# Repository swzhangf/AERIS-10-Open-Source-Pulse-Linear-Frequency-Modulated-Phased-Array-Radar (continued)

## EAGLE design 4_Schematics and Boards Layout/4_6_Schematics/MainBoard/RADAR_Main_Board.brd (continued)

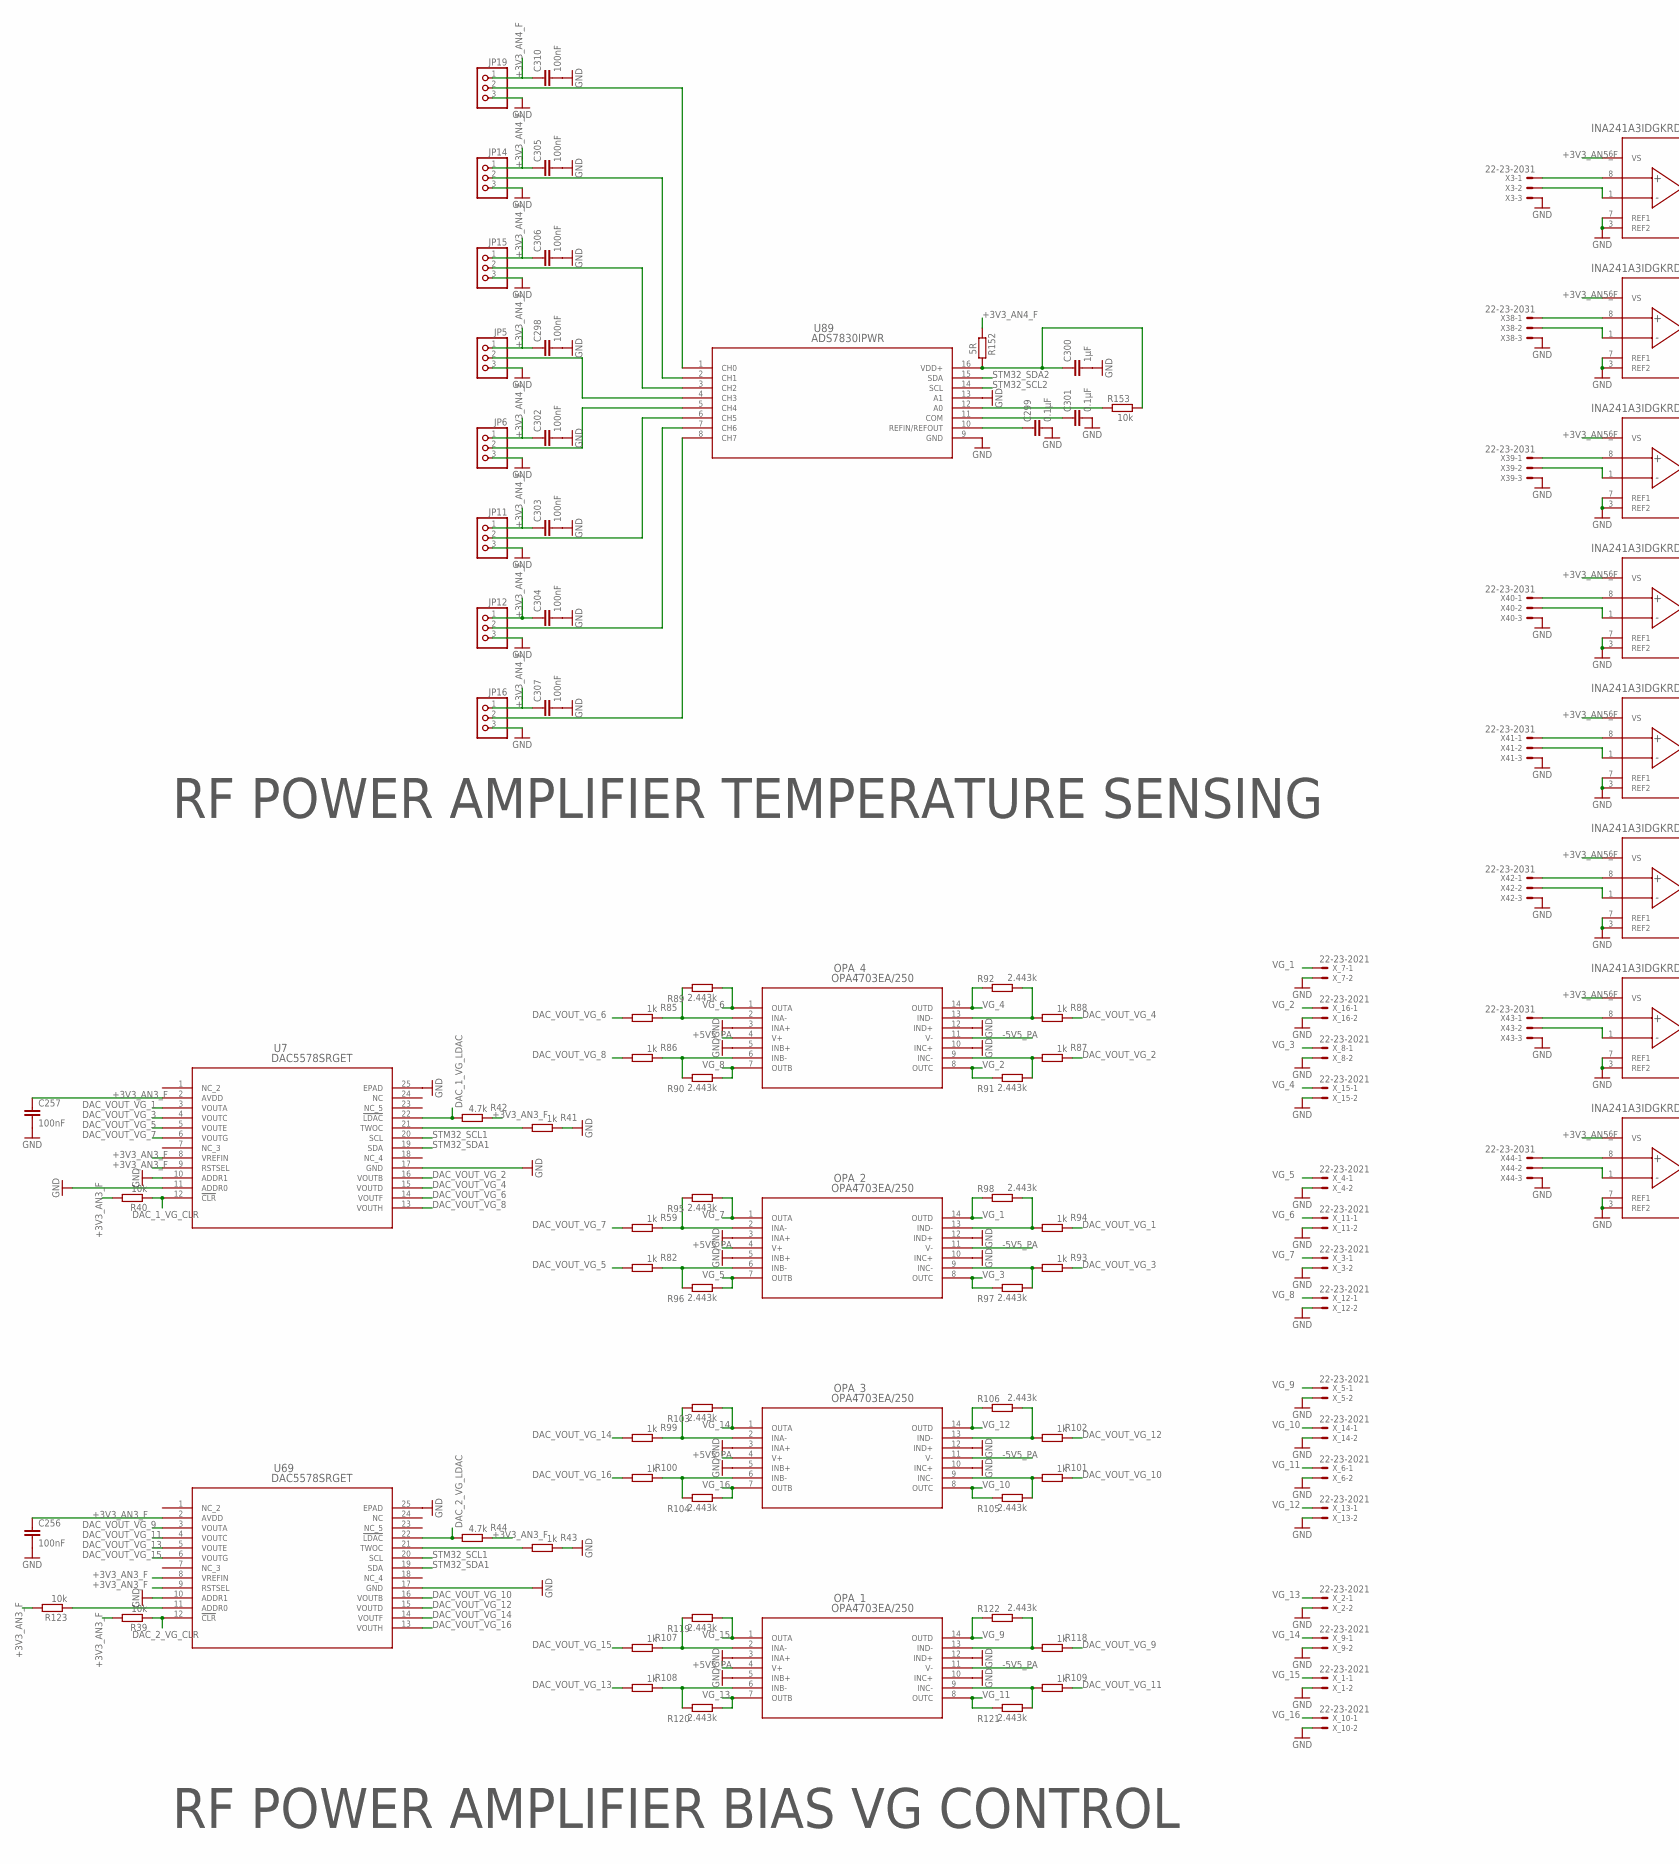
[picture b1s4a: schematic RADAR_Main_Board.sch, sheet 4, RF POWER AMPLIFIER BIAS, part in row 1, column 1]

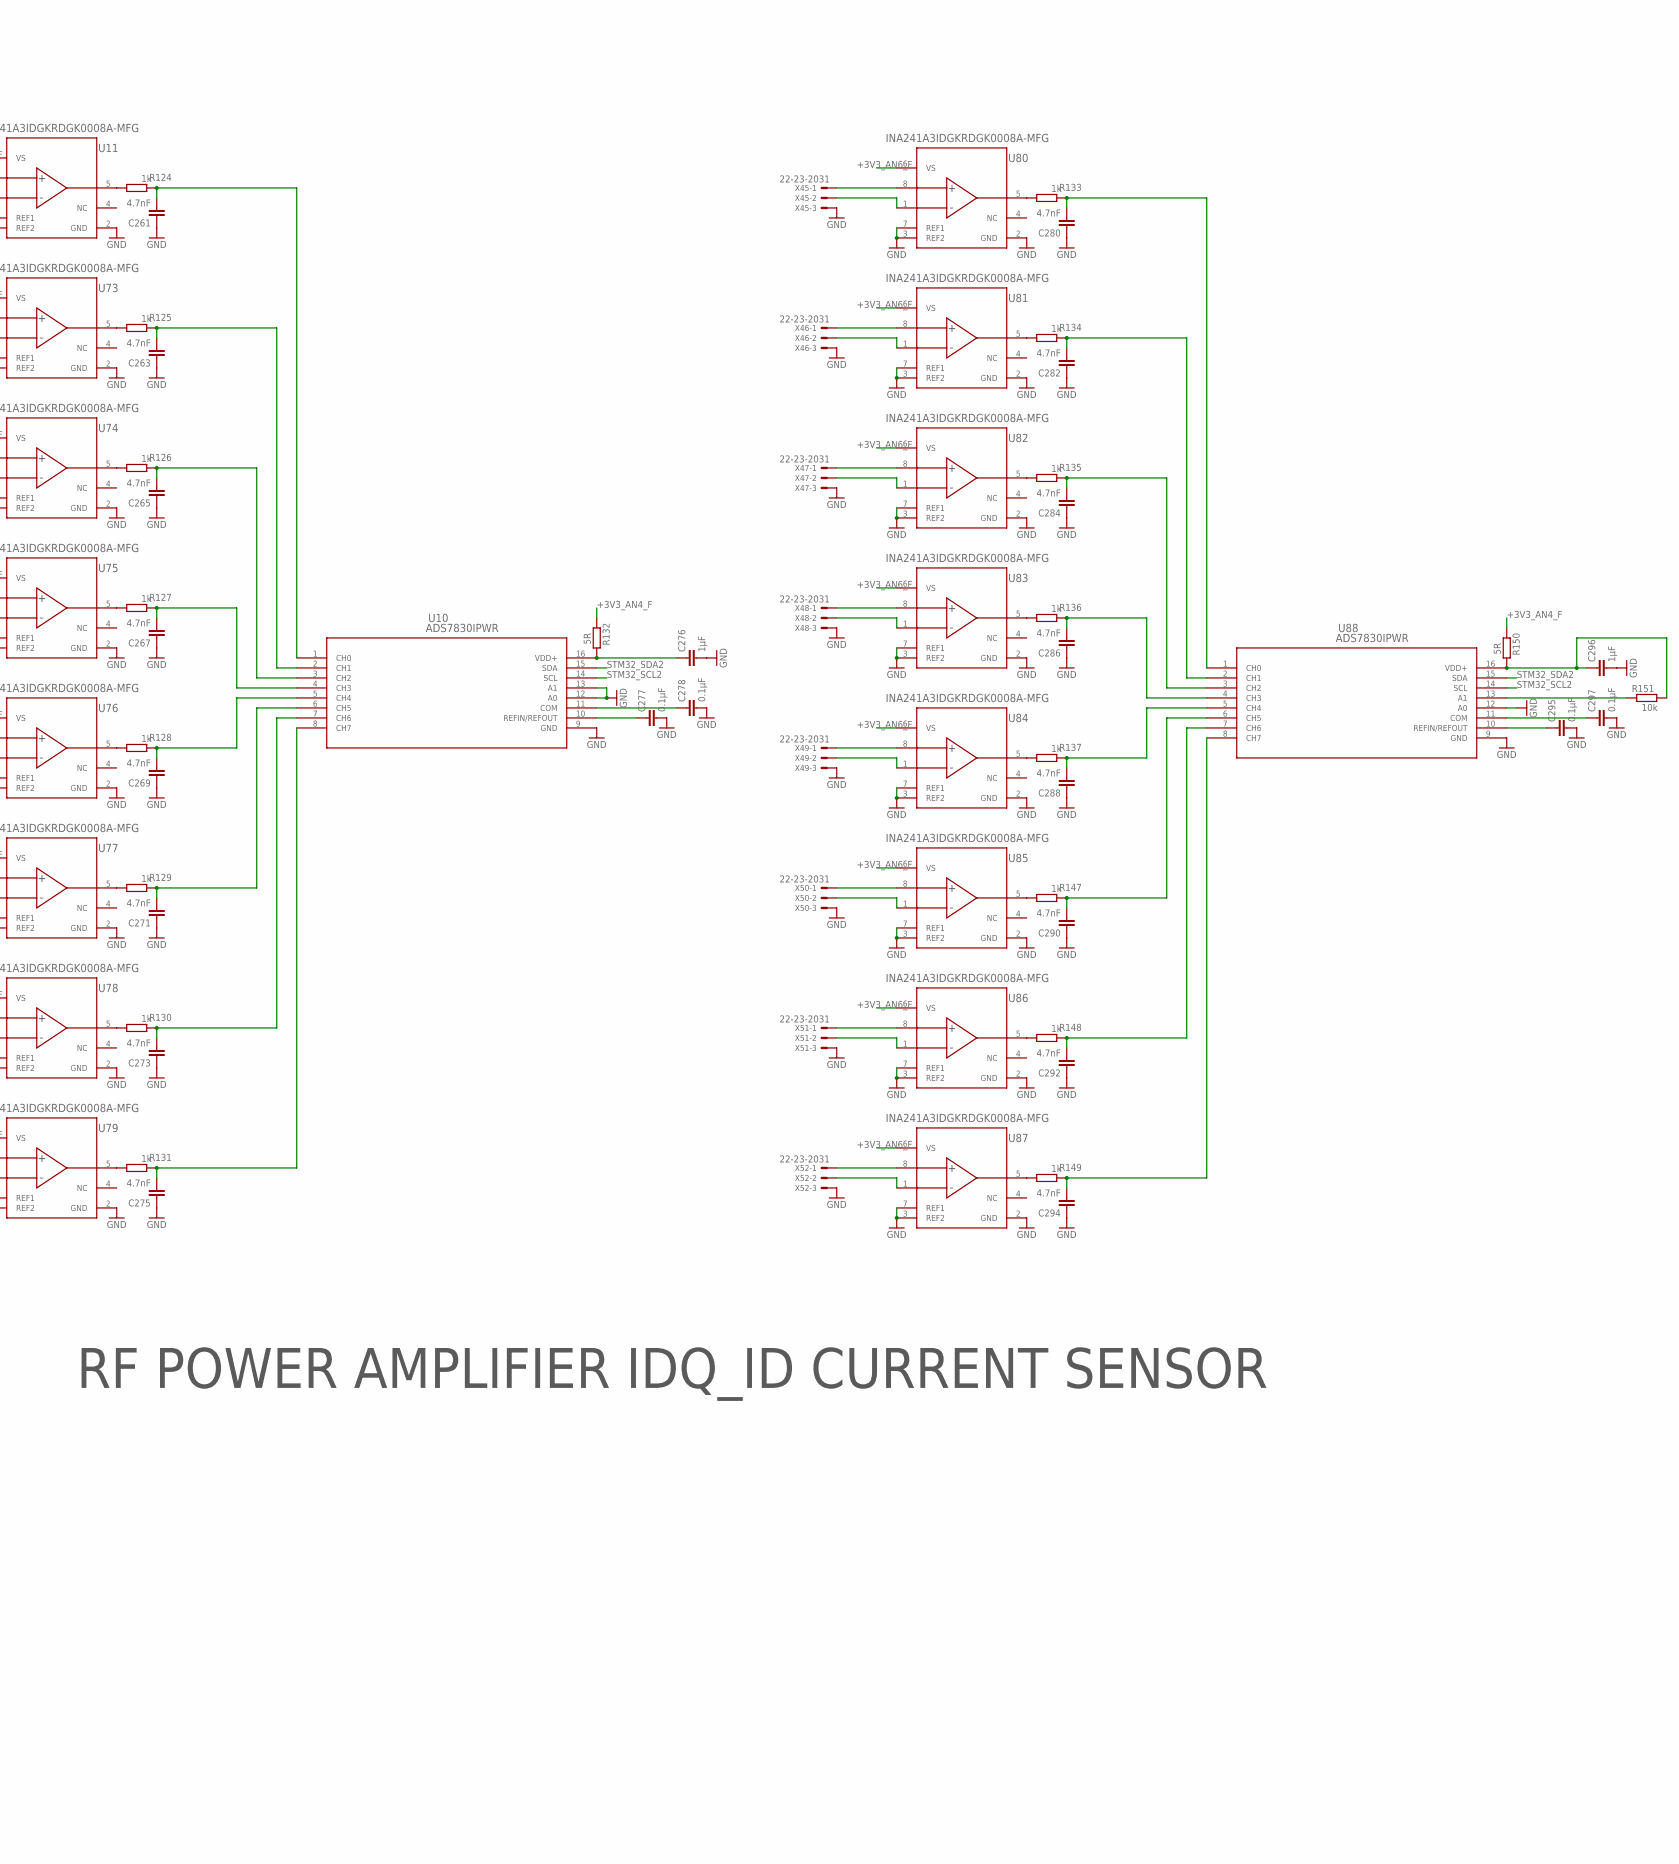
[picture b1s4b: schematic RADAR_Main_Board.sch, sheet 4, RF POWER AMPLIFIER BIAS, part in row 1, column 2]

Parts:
C256, C257, C298, C302, C303, C304, C305, C306, C307, C310: 100nF; C0201
C261, C263, C265, C267, C269, C271, C273, C275, C280, C282, C284, C286, C288, C290, C292, C294: 4.7nF; C0201
C276, C296, C300: 1µF; C0201
C277, C278, C295, C297, C299, C301: 0.1µF; C0201
JP5, JP6, JP11, JP12, JP14, JP15, JP16, JP19: PINHD-1X3; 1X03
OPA_1, OPA_2, OPA_3, OPA_4: OPA4703EA/250; PW14
R39, R40, R123, R151, R153: 10k; R0201
R41, R43, R59, R82, R85, R86, R87, R88, R93, R94, R99, R100, R101, R102, R107, R108, R109, R118, R124, R125, R126, R127, R128, R129, R130, R131, R133, R134, R135, R136, R137, R147, R148, R149: 1k; R0201
R42, R44: 4.7k; R0201
R89, R90, R91, R92, R95, R96, R97, R98, R103, R104, R105, R106, R119, R120, R121, R122: 2.443k; R0201
R132, R150, R152: 5R; R0201
U7, U69: DAC5578SRGET; RGE24_2P7X2P7
U10, U88, U89: ADS7830IPWR; PW16
U11, U73, U74, U75, U76, U77, U78, U79, U80, U81, U82, U83, U84, U85, U86, U87: INA241A3IDGKRDGK0008A-MFG; DGK0008A-MFG
X3, X38, X39, X40, X41, X42, X43, X44, X45, X46, X47, X48, X49, X50, X51, X52: 22-23-2031
X_1, X_2, X_3, X_4, X_5, X_6, X_7, X_8, X_9, X_10, X_11, X_12, X_13, X_14, X_15, X_16: 22-23-2021

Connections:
+3V3_AN3_F: C256.1, C257.1, R39.2, R40.2, R42.1, R44.1, R123.2, U7.2 (AVDD), U7.8 (VREFIN), U7.9 (RSTSEL), U69.2 (AVDD), U69.8 (VREFIN), U69.9 (RSTSEL); also elsewhere on the board
+3V3_AN4_F: C298.1, C302.1, C303.1, C304.1, C305.1, C306.1, C307.1, C310.1, JP5.1, JP6.1, JP11.1, JP12.1, JP14.1, JP15.1, JP16.1, JP19.1, R132.1, R150.1, R152.1; also elsewhere on the board
+3V3_AN5_F: U11.6 (VS), U73.6 (VS), U74.6 (VS), U75.6 (VS), U76.6 (VS), U77.6 (VS), U78.6 (VS), U79.6 (VS); also elsewhere on the board
+3V3_AN6_F: U80.6 (VS), U81.6 (VS), U82.6 (VS), U83.6 (VS), U84.6 (VS), U85.6 (VS), U86.6 (VS), U87.6 (VS); also elsewhere on the board
+5V5_PA: OPA_1.4 (V+), OPA_2.4 (V+), OPA_3.4 (V+), OPA_4.4 (V+); also elsewhere on the board
-5V5_PA: OPA_1.11 (V-), OPA_2.11 (V-), OPA_3.11 (V-), OPA_4.11 (V-); also elsewhere on the board
DAC_1_VG_CLR: R40.1, U7.12 (!CLR); also elsewhere on the board
DAC_1_VG_LDAC: R42.2, U7.22 (!LDAC); also elsewhere on the board
DAC_2_VG_CLR: R39.1, U69.12 (!CLR); also elsewhere on the board
DAC_2_VG_LDAC: R44.2, U69.22 (!LDAC); also elsewhere on the board
DAC_VOUT_VG_1: R94.1, U7.3 (VOUTA)
DAC_VOUT_VG_2: R87.1, U7.16 (VOUTB)
DAC_VOUT_VG_3: R93.1, U7.4 (VOUTC)
DAC_VOUT_VG_4: R88.1, U7.15 (VOUTD)
DAC_VOUT_VG_5: R82.2, U7.5 (VOUTE)
DAC_VOUT_VG_6: R85.2, U7.14 (VOUTF)
DAC_VOUT_VG_7: R59.2, U7.6 (VOUTG)
DAC_VOUT_VG_8: R86.2, U7.13 (VOUTH)
DAC_VOUT_VG_9: R118.1, U69.3 (VOUTA)
DAC_VOUT_VG_10: R101.1, U69.16 (VOUTB)
DAC_VOUT_VG_11: R109.1, U69.4 (VOUTC)
DAC_VOUT_VG_12: R102.1, U69.15 (VOUTD)
DAC_VOUT_VG_13: R108.2, U69.5 (VOUTE)
DAC_VOUT_VG_14: R99.2, U69.14 (VOUTF)
DAC_VOUT_VG_15: R107.2, U69.6 (VOUTG)
DAC_VOUT_VG_16: R100.2, U69.13 (VOUTH)
GND: C256.2, C257.2, C261.1, C263.1, C265.1, C267.1, C269.1, C271.1, C273.1, C275.1, C276.2, C277.2, C278.2, C280.1, C282.1, C284.1, C286.1, C288.1, C290.1, C292.1, C294.1, C295.2, C296.2, C297.2, C298.2, C299.2, C300.2, C301.2, C302.2, C303.2, C304.2, C305.2, C306.2, C307.2, C310.2, JP5.3, JP6.3, JP11.3, JP12.3, JP14.3, JP15.3, JP16.3, JP19.3, OPA_1.3 (INA+), OPA_1.5 (INB+), OPA_1.10 (INC+), OPA_1.12 (IND+), OPA_2.3 (INA+), OPA_2.5 (INB+), OPA_2.10 (INC+), OPA_2.12 (IND+), OPA_3.3 (INA+), OPA_3.5 (INB+), OPA_3.10 (INC+), OPA_3.12 (IND+), OPA_4.3 (INA+), OPA_4.5 (INB+), OPA_4.10 (INC+), OPA_4.12 (IND+), R41.1, R43.1, U7.10 (ADDR1), U7.11 (ADDR0), U7.17 (GND), U7.25 (EPAD), U10.9 (GND), U10.12 (A0), U10.13 (A1), U11.2 (GND), U11.3 (REF2), U11.7 (REF1), U69.10 (ADDR1), U69.17 (GND), U69.25 (EPAD), U73.2 (GND), U73.3 (REF2), U73.7 (REF1), U74.2 (GND), U74.3 (REF2), U74.7 (REF1), U75.2 (GND), U75.3 (REF2), U75.7 (REF1), U76.2 (GND), U76.3 (REF2), U76.7 (REF1), U77.2 (GND), U77.3 (REF2), U77.7 (REF1), U78.2 (GND), U78.3 (REF2), U78.7 (REF1), U79.2 (GND), U79.3 (REF2), U79.7 (REF1), U80.2 (GND), U80.3 (REF2), U80.7 (REF1), U81.2 (GND), U81.3 (REF2), U81.7 (REF1), U82.2 (GND), U82.3 (REF2), U82.7 (REF1), U83.2 (GND), U83.3 (REF2), U83.7 (REF1), U84.2 (GND), U84.3 (REF2), U84.7 (REF1), U85.2 (GND), U85.3 (REF2), U85.7 (REF1), U86.2 (GND), U86.3 (REF2), U86.7 (REF1), U87.2 (GND), U87.3 (REF2), U87.7 (REF1), U88.9 (GND), U88.12 (A0), U89.9 (GND), U89.13 (A1), X3.3, X38.3, X39.3, X40.3, X41.3, X42.3, X43.3, X44.3, X45.3, X46.3, X47.3, X48.3, X49.3, X50.3, X51.3, X52.3, X_1.2, X_2.2, X_3.2, X_4.2, X_5.2, X_6.2, X_7.2, X_8.2, X_9.2, X_10.2, X_11.2, X_12.2, X_13.2, X_14.2, X_15.2, X_16.2; also elsewhere on the board
unnamed: R123.1, U69.11 (ADDR0)
unnamed: R43.2, U69.21 (TWOC)
unnamed: OPA_4.2 (INA-), R85.1, R89.1
unnamed: U11.8 (IN+), X3.1
unnamed: OPA_4.6 (INB-), R86.1, R90.1
unnamed: U11.1 (IN-), X3.2
unnamed: R124.2, U11.5 (OUT)
unnamed: C261.2, R124.1, U10.1 (CH0)
unnamed: U73.8 (IN+), X38.1
unnamed: OPA_4.9 (INC-), R87.2, R91.2
unnamed: U73.1 (IN-), X38.2
unnamed: R125.2, U73.5 (OUT)
unnamed: OPA_4.13 (IND-), R88.2, R92.2
unnamed: C263.2, R125.1, U10.2 (CH1)
unnamed: U74.8 (IN+), X39.1
unnamed: U74.1 (IN-), X39.2
unnamed: R126.2, U74.5 (OUT)
unnamed: R41.2, U7.21 (TWOC)
unnamed: OPA_2.2 (INA-), R59.1, R95.1
unnamed: C265.2, R126.1, U10.3 (CH2)
unnamed: OPA_2.6 (INB-), R82.1, R96.1
unnamed: U75.8 (IN+), X40.1
unnamed: U75.1 (IN-), X40.2
unnamed: R127.2, U75.5 (OUT)
unnamed: OPA_2.9 (INC-), R93.2, R97.2
unnamed: C267.2, R127.1, U10.4 (CH3)
unnamed: U76.8 (IN+), X41.1
unnamed: OPA_2.13 (IND-), R94.2, R98.2
unnamed: U76.1 (IN-), X41.2
unnamed: R128.2, U76.5 (OUT)
unnamed: C269.2, R128.1, U10.5 (CH4)
unnamed: U77.8 (IN+), X42.1
unnamed: U77.1 (IN-), X42.2
unnamed: R129.2, U77.5 (OUT)
unnamed: OPA_3.2 (INA-), R99.1, R103.1
unnamed: C271.2, R129.1, U10.6 (CH5)
unnamed: OPA_3.6 (INB-), R100.1, R104.1
unnamed: U78.8 (IN+), X43.1
unnamed: U78.1 (IN-), X43.2
unnamed: R130.2, U78.5 (OUT)
unnamed: OPA_3.9 (INC-), R101.2, R105.2
unnamed: C273.2, R130.1, U10.7 (CH6)
unnamed: U79.8 (IN+), X44.1
unnamed: OPA_3.13 (IND-), R102.2, R106.2
unnamed: U79.1 (IN-), X44.2
unnamed: R131.2, U79.5 (OUT)
unnamed: C275.2, R131.1, U10.8 (CH7)
unnamed: C277.1, U10.10 (REFIN/REFOUT)
unnamed: C276.1, R132.2, U10.16 (VDD+)
unnamed: C278.1, U10.11 (COM)
unnamed: OPA_1.2 (INA-), R107.1, R119.1
unnamed: U80.8 (IN+), X45.1
unnamed: OPA_1.6 (INB-), R108.1, R120.1
unnamed: U80.1 (IN-), X45.2
unnamed: R133.2, U80.5 (OUT)
unnamed: C280.2, R133.1, U88.1 (CH0)
unnamed: OPA_1.9 (INC-), R109.2, R121.2
unnamed: U81.8 (IN+), X46.1
unnamed: U81.1 (IN-), X46.2
unnamed: OPA_1.13 (IND-), R118.2, R122.2
unnamed: R134.2, U81.5 (OUT)
unnamed: C282.2, R134.1, U88.2 (CH1)
unnamed: U82.8 (IN+), X47.1
unnamed: U82.1 (IN-), X47.2
unnamed: R135.2, U82.5 (OUT)
unnamed: C284.2, R135.1, U88.3 (CH2)
unnamed: U83.8 (IN+), X48.1
unnamed: U83.1 (IN-), X48.2
unnamed: R136.2, U83.5 (OUT)
unnamed: C286.2, R136.1, U88.4 (CH3)
unnamed: U84.8 (IN+), X49.1
unnamed: U84.1 (IN-), X49.2
unnamed: R137.2, U84.5 (OUT)
unnamed: C288.2, R137.1, U88.5 (CH4)
unnamed: U85.8 (IN+), X50.1
unnamed: U85.1 (IN-), X50.2
unnamed: R147.2, U85.5 (OUT)
unnamed: C290.2, R147.1, U88.6 (CH5)
unnamed: U86.8 (IN+), X51.1
unnamed: U86.1 (IN-), X51.2
unnamed: R148.2, U86.5 (OUT)
unnamed: C292.2, R148.1, U88.7 (CH6)
unnamed: U87.8 (IN+), X52.1
unnamed: U87.1 (IN-), X52.2
unnamed: R149.2, U87.5 (OUT)
unnamed: C294.2, R149.1, U88.8 (CH7)
unnamed: C295.1, U88.10 (REFIN/REFOUT)
unnamed: C296.1, R150.2, R151.2, U88.16 (VDD+)
unnamed: C297.1, U88.11 (COM)
unnamed: R151.1, U88.13 (A1)
unnamed: R153.1, U89.12 (A0)
unnamed: JP5.2, U89.4 (CH3)
unnamed: JP6.2, U89.5 (CH4)
unnamed: JP19.2, U89.1 (CH0)
unnamed: JP12.2, U89.7 (CH6)
unnamed: JP14.2, U89.2 (CH1)
unnamed: JP16.2, U89.8 (CH7)
unnamed: C299.1, U89.10 (REFIN/REFOUT)
unnamed: C300.1, R152.2, R153.2, U89.16 (VDD+)
unnamed: C301.1, U89.11 (COM)
unnamed: JP11.2, U89.6 (CH5)
unnamed: JP15.2, U89.3 (CH2)
STM32_SCL1: U7.20 (SCL), U69.20 (SCL); also elsewhere on the board
STM32_SCL2: U10.14 (SCL), U88.14 (SCL), U89.14 (SCL); also elsewhere on the board
STM32_SDA1: U7.19 (SDA), U69.19 (SDA); also elsewhere on the board
STM32_SDA2: U10.15 (SDA), U88.15 (SDA), U89.15 (SDA); also elsewhere on the board
VG_1: OPA_2.14 (OUTD), R98.1, X_7.1
VG_2: OPA_4.8 (OUTC), R91.1, X_16.1
VG_3: OPA_2.8 (OUTC), R97.1, X_8.1
VG_4: OPA_4.14 (OUTD), R92.1, X_15.1
VG_5: OPA_2.7 (OUTB), R96.2, X_4.1
VG_6: OPA_4.1 (OUTA), R89.2, X_11.1
VG_7: OPA_2.1 (OUTA), R95.2, X_3.1
VG_8: OPA_4.7 (OUTB), R90.2, X_12.1
VG_9: OPA_1.14 (OUTD), R122.1, X_5.1
VG_10: OPA_3.8 (OUTC), R105.1, X_14.1
VG_11: OPA_1.8 (OUTC), R121.1, X_6.1
VG_12: OPA_3.14 (OUTD), R106.1, X_13.1
VG_13: OPA_1.7 (OUTB), R120.2, X_2.1
VG_14: OPA_3.1 (OUTA), R103.2, X_9.1
VG_15: OPA_1.1 (OUTA), R119.2, X_1.1
VG_16: OPA_3.7 (OUTB), R104.2, X_10.1

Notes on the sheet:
RF POWER AMPLIFIER IDQ_ID CURRENT SENSOR
RF POWER AMPLIFIER BIAS VG CONTROL
RF POWER AMPLIFIER TEMPERATURE SENSING

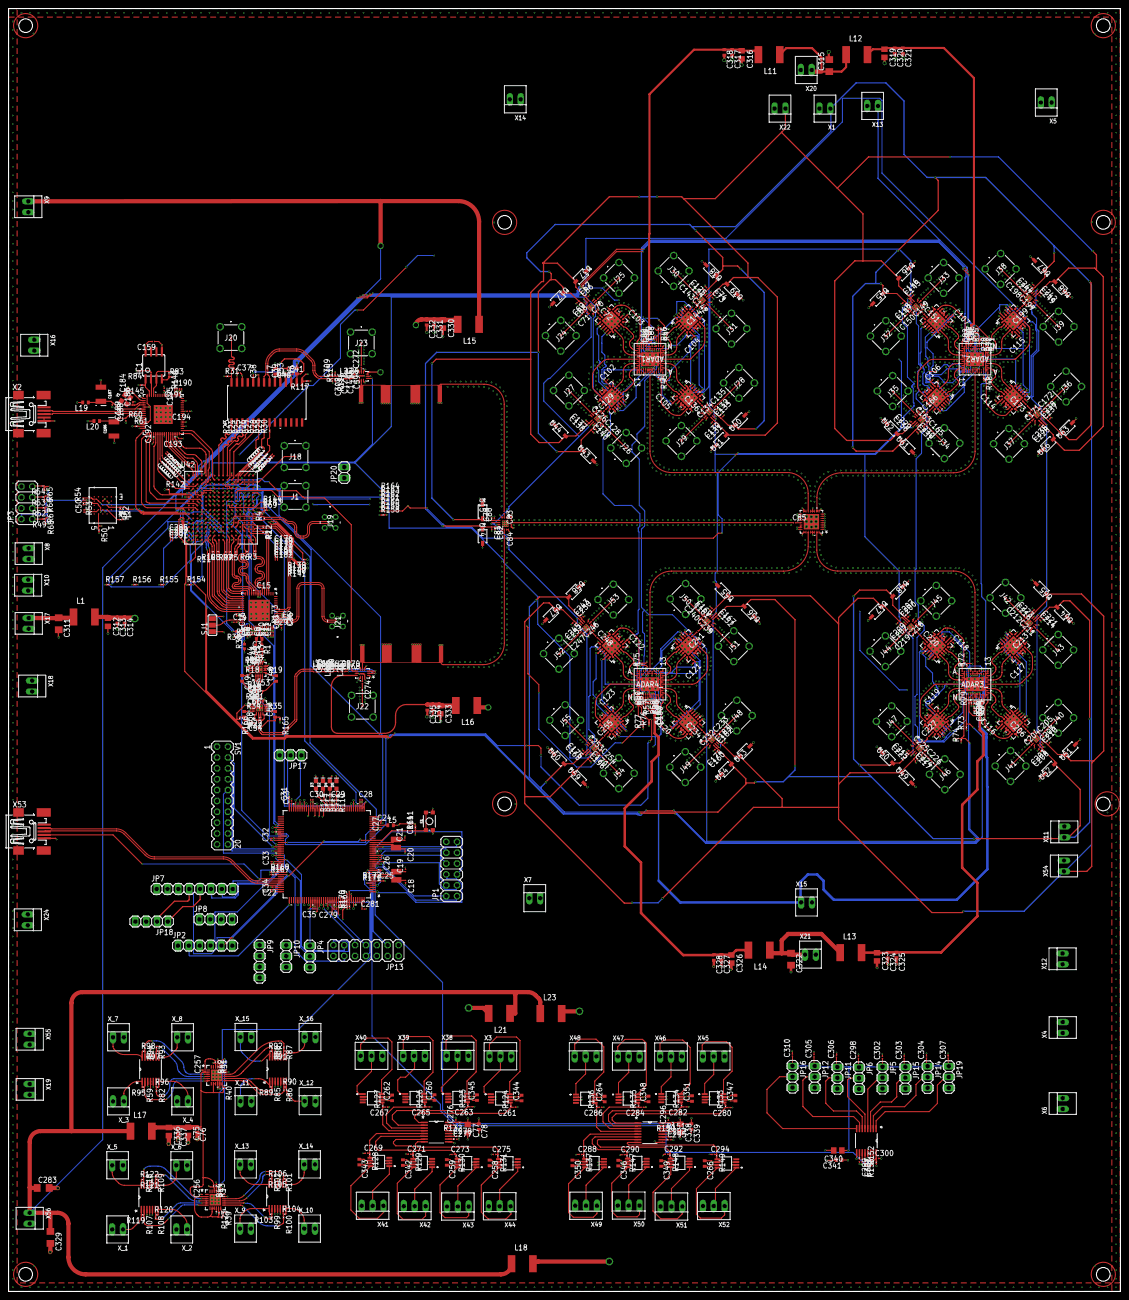
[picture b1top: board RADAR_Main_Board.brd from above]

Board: 10 copper layers, 260.0 x 300.0 mm, 789 parts (0 on the bottom side), 649 nets.

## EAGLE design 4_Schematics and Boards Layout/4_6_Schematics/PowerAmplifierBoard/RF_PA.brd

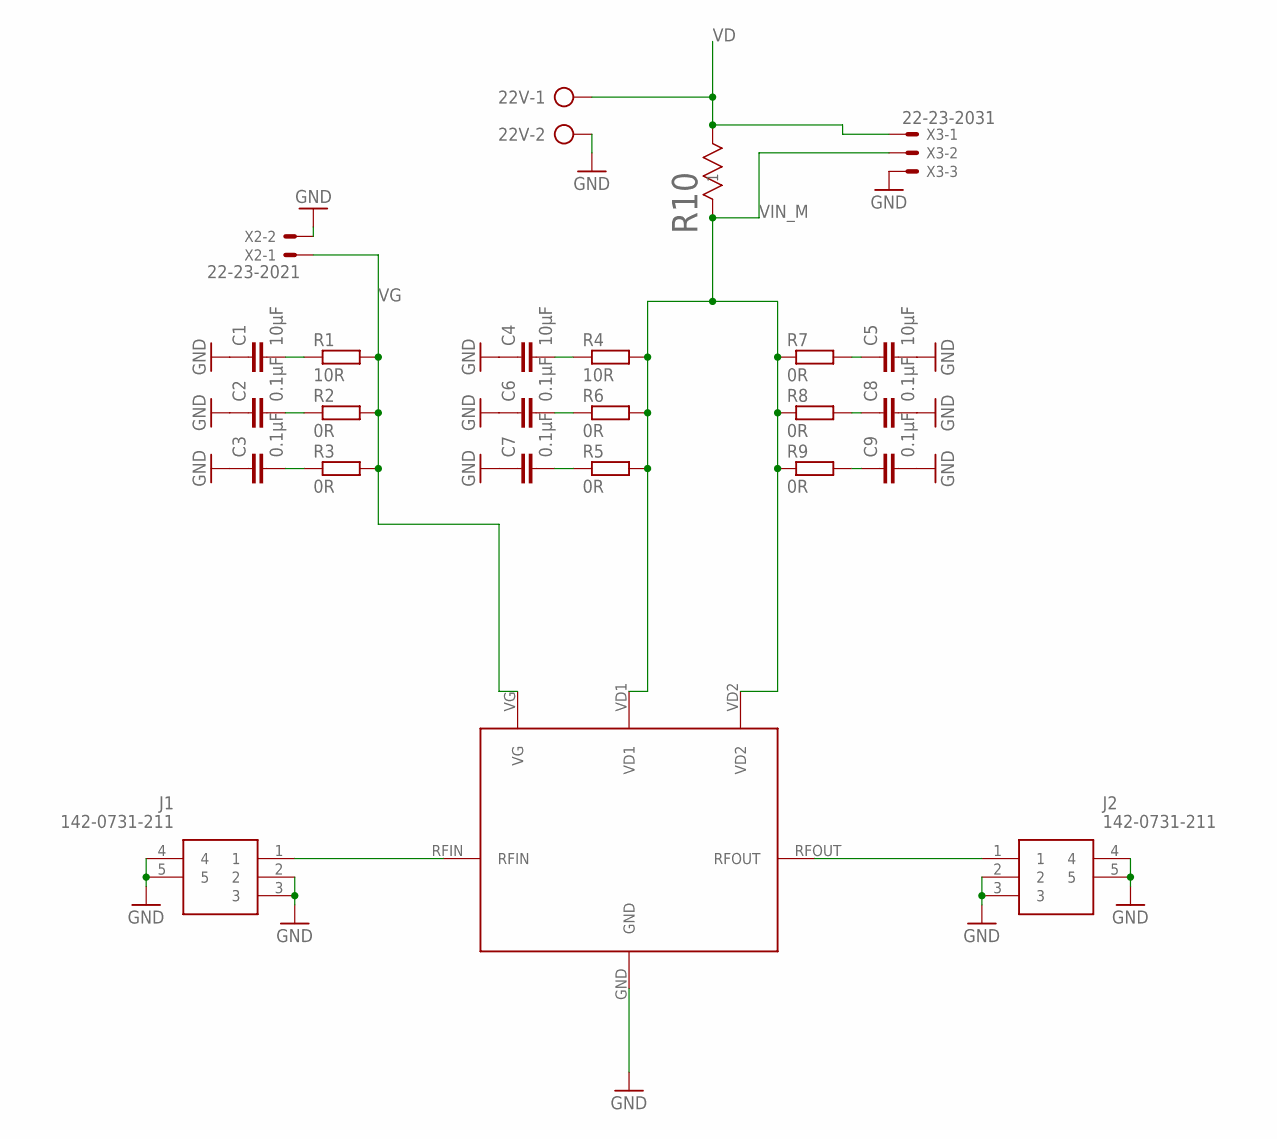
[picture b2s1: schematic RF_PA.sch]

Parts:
22V: AK300/2
C1, C4, C5: 10µF; C1206
C2, C3, C6, C7, C8, C9: 0.1µF; C0402
J1, J2: 142-0731-211; 1420731211
R1, R4: 10R; R0402
R2, R3, R5, R7, R8, R9: 0R; R0402
R6: 0R; R0603
R10: 5mR; WSL2816_VIS
U$1: QPA2962_B
X2: 22-23-2021
X3: 22-23-2031

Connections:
GND: 22V.2, C1.1, C2.1, C3.1, C4.1, C5.2, C6.1, C7.1, C8.2, C9.2, J1.2, J1.3, J1.4, J1.5, J2.2, J2.3, J2.4, J2.5, U$1.GND, X2.2, X3.3
unnamed: C3.2, R3.1
unnamed: J1.1, U$1.RFIN
unnamed: C1.2, R1.1
unnamed: C2.2, R2.1
unnamed: C4.2, R4.1
unnamed: C6.2, R6.1
unnamed: C7.2, R5.1
unnamed: J2.1, U$1.RFOUT
unnamed: C5.1, R7.2
unnamed: C8.1, R8.2
unnamed: C9.1, R9.2
VD: 22V.1, R10.2, X3.1
VG: R1.2, R2.2, R3.2, U$1.VG, X2.1
VIN_M: R4.2, R5.2, R6.2, R7.1, R8.1, R9.1, R10.1, U$1.VD1, U$1.VD2, X3.2

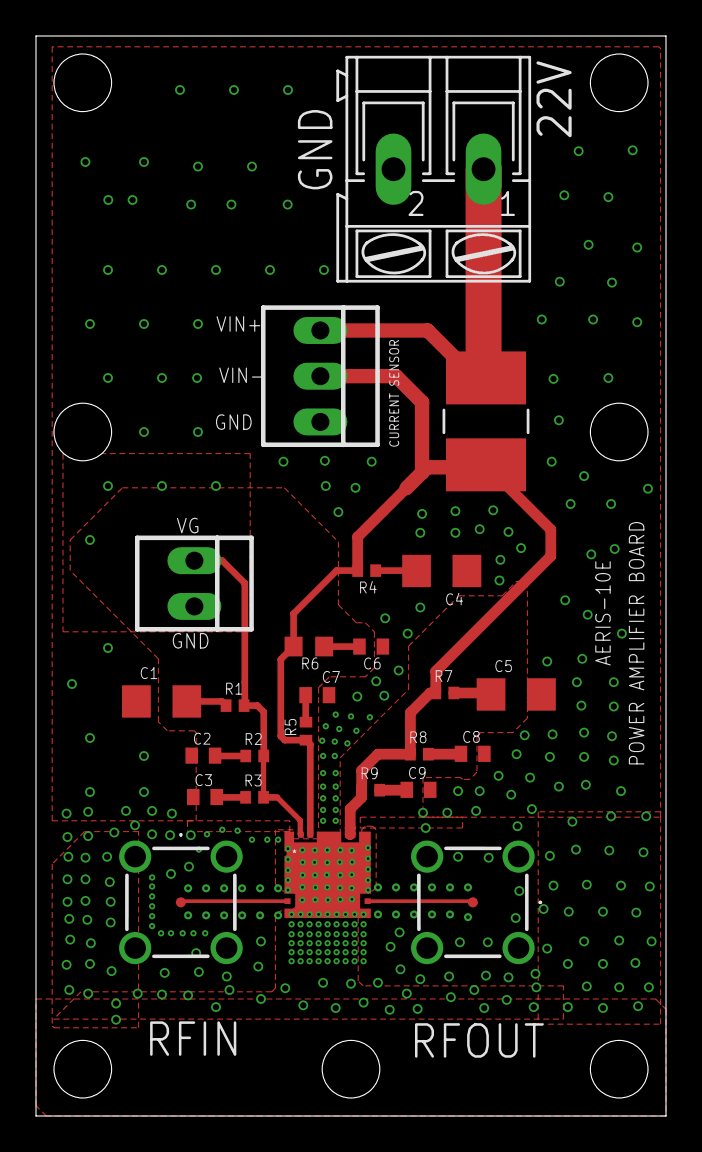
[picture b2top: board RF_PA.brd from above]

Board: 4 copper layers, 35.0 x 60.0 mm, 25 parts (0 on the bottom side), 15 nets.
